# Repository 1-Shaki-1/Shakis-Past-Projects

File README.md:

# Shakis-Past-Projects
Some past projects that I made along the way

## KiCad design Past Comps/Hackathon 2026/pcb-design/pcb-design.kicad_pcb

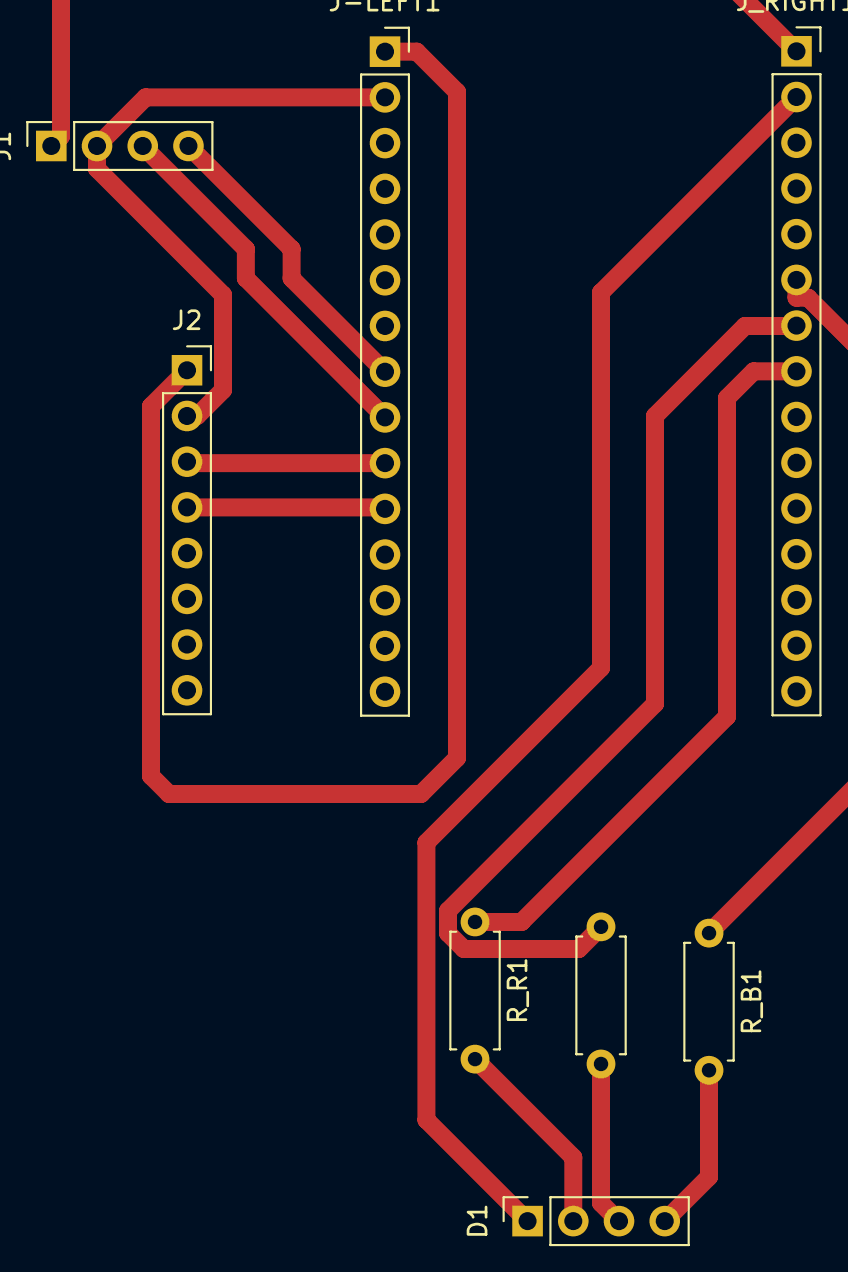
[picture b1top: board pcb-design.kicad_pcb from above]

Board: 2 copper layers, 8 parts (0 on the bottom side), 14 nets.

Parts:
D1: LED_ARGB; PinSocket_1x04_P2.54mm_Vertical
J1: A02YYUW; PinSocket_1x04_P2.54mm_Vertical
J2: MPU-6050; PinSocket_1x08_P2.54mm_Vertical
J-LEFT1: USB C CABLE; PinSocket_1x15_P2.54mm_Vertical
J_RIGHT1: Conn_01x15_Socket; PinSocket_1x15_P2.54mm_Vertical
R_B1: 330; R_Axial_DIN0207_L6.3mm_D2.5mm_P7.62mm_Horizontal
R_G1: 330; R_Axial_DIN0207_L6.3mm_D2.5mm_P7.62mm_Horizontal
R_R1: 330; R_Axial_DIN0207_L6.3mm_D2.5mm_P7.62mm_Horizontal

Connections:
unnamed: D1.1 (A), J_RIGHT1.2
unnamed: D1.4 (BK), R_B1.2
unnamed: D1.3 (GK), R_G1.2
unnamed: D1.2 (RK), R_R1.2
unnamed: J1.1, J_RIGHT1.1
unnamed: J2.1, J-LEFT1.1
unnamed: J1.2, J2.2, J-LEFT1.2
unnamed: J1.4, J-LEFT1.8
unnamed: J1.3, J-LEFT1.9
unnamed: J2.3, J-LEFT1.10
unnamed: J2.4, J-LEFT1.11
unnamed: J_RIGHT1.6, R_B1.1
unnamed: J_RIGHT1.7, R_G1.1
unnamed: J_RIGHT1.8, R_R1.1

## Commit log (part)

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2026-02-15 Website/ Arduino code dump
2026-02-15 Adding Arduino Projects
2026-02-15 arduino commit
2026-02-15 created README for tej3m
2026-03-14 test signed commit
